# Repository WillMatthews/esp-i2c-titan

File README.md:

# esp-i2c-titan
nodemcu breakout board to drive overview titan

## Kicad/
Contains the PCB layout to drive an Overview titan through flatflex connector J2.

## arduino/
Contains the arduino code required to program an ESP8266 nodeMCU dev board to interface with the polariser.

## matlab/
Contains MATLAB code to interface with the ESP8266 over a serial interface.

## todo:
- CAD mount for the polariser.

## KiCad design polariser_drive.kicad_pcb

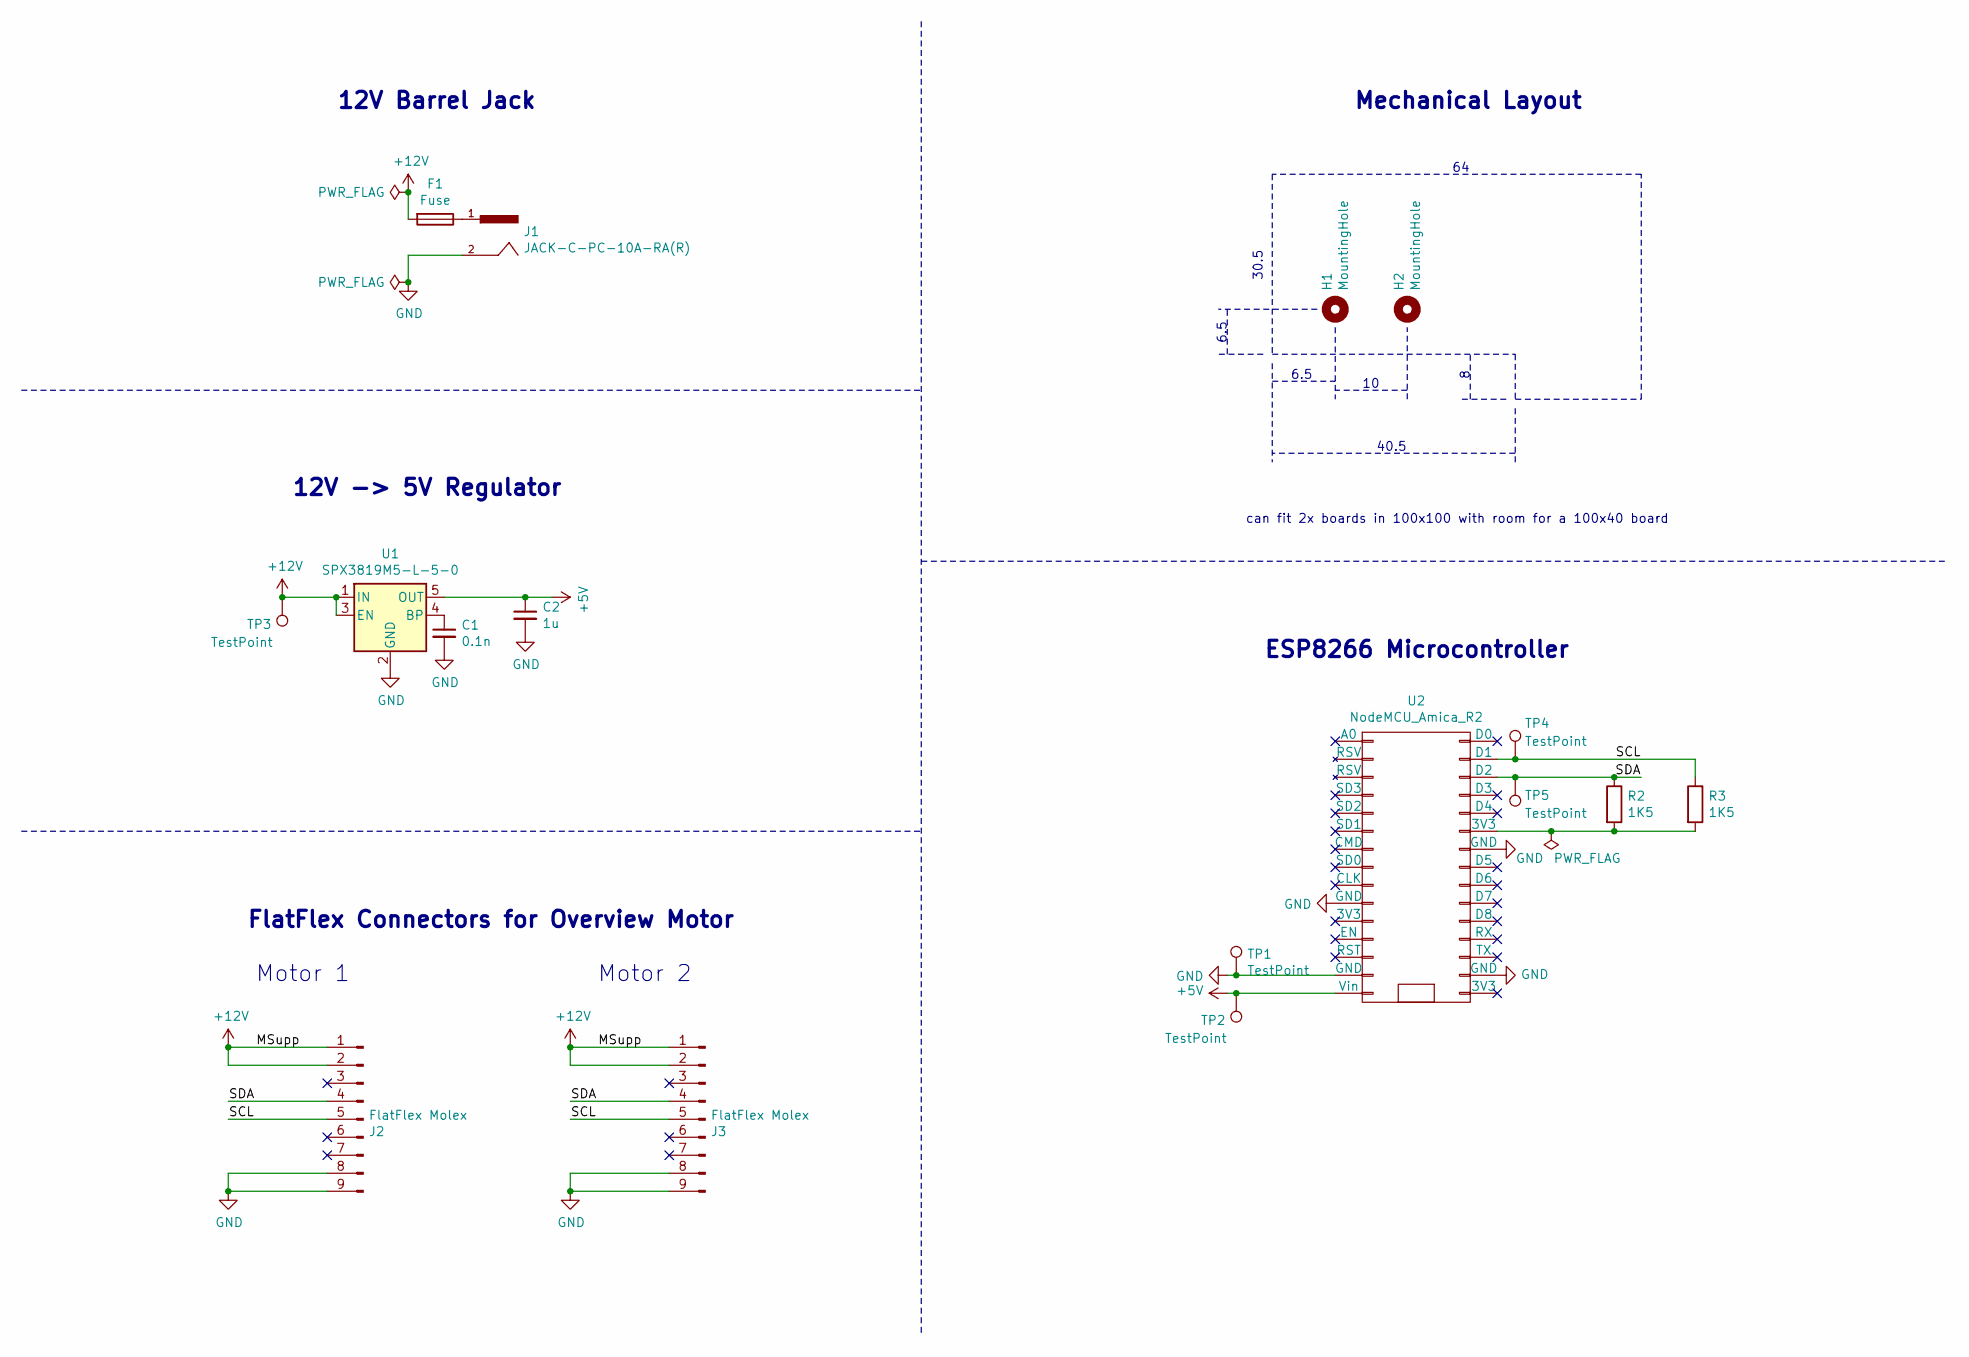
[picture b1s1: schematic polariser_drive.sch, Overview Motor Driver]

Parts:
C1: 0.1n; Fuse_1206_3216Metric_Pad1.42x1.75mm_HandSolder
C2: 1u; C_0805_2012Metric_Pad1.15x1.40mm_HandSolder
F1: Fuse; R_Axial_DIN0309_L9.0mm_D3.2mm_P12.70mm_Horizontal
H1, H2: MountingHole; MountingHole_4.3mm_M4
J1: JACK-C-PC-10A-RA(R); GLOBTECK_JACK-C-PC-10A-RA(R); Part 1939-1434-ND
J2, J3: FlatFlex Molex; 9pos; PartA WM7958CT-ND
R2, R3: 1K5; R_0805_2012Metric
TP1, TP2, TP3: TestPoint; TestPoint_Pad_D1.5mm
TP4, TP5: TestPoint; PinHeader_1x01_P2.54mm_Vertical
U1: SPX3819M5-L-5-0; SOT-23-5; Part 1016-1874-1-ND
U2: NodeMCU_Amica_R2

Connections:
+5V: C2.1, TP2.1, U1.5 (OUT), U2.15 (Vin)
+12V: F1.2, J2.1, J2.2, J3.1, J3.2, TP3.1, U1.1 (IN), U1.3 (EN)
/SCL: J2.5, J3.5, R3.1, TP4.1, U2.29 (D1)
/SDA: J2.4, J3.4, R2.1, TP5.1, U2.28 (D2)
GND: C1.2, C2.2, J1.2, J2.8, J2.9, J3.8, J3.9, TP1.1, U1.2 (GND), U2.10 (GND), U2.14 (GND), U2.17 (GND), U2.24 (GND)
unnamed: C1.1, U1.4 (BP)
unnamed: F1.1, J1.1
unnamed: R2.2, R3.2, U2.25 (3V3)

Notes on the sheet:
ESP8266 Microcontroller
can fit 2x boards in 100x100 with room for a 100x40 board
Mechanical Layout
12V -> 5V Regulator
12V Barrel Jack
FlatFlex Connectors for Overview Motor
Motor 2
Motor 1
6.5
40.5
30.5

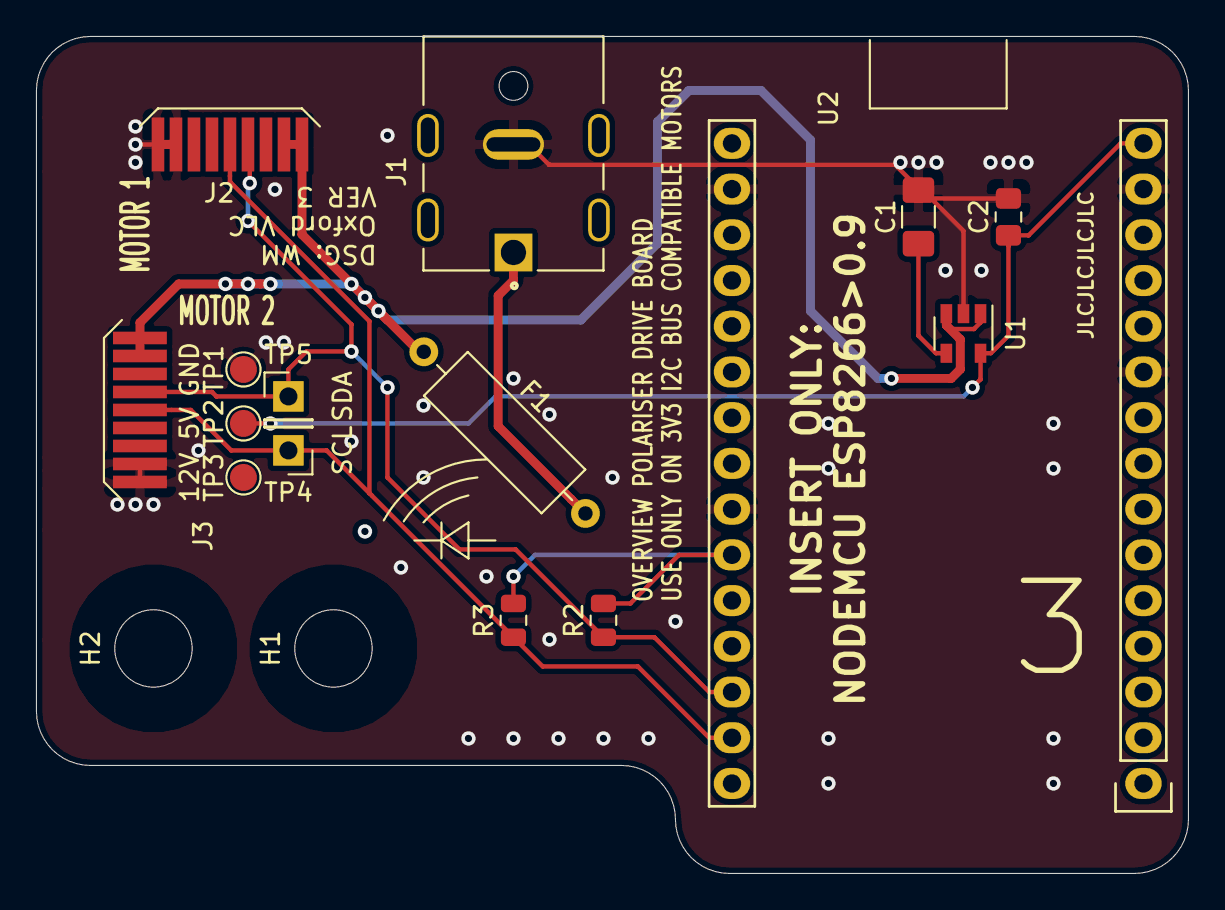
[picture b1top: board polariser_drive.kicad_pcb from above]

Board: 2 copper layers, 64.0 x 46.5 mm, 17 parts (0 on the bottom side), 8 nets.

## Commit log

2020-03-14 board first ver
2020-03-16 add another connector and configurable address lines
2020-03-16 add note on sch
2020-04-24 stupid rookie footprint error
2020-06-22 board finished
2020-06-22 added arduino code and matlab drive code
2020-06-22 commented matlab code
2022-08-18 Create LICENCE
2024-04-06 add noddy board mount
